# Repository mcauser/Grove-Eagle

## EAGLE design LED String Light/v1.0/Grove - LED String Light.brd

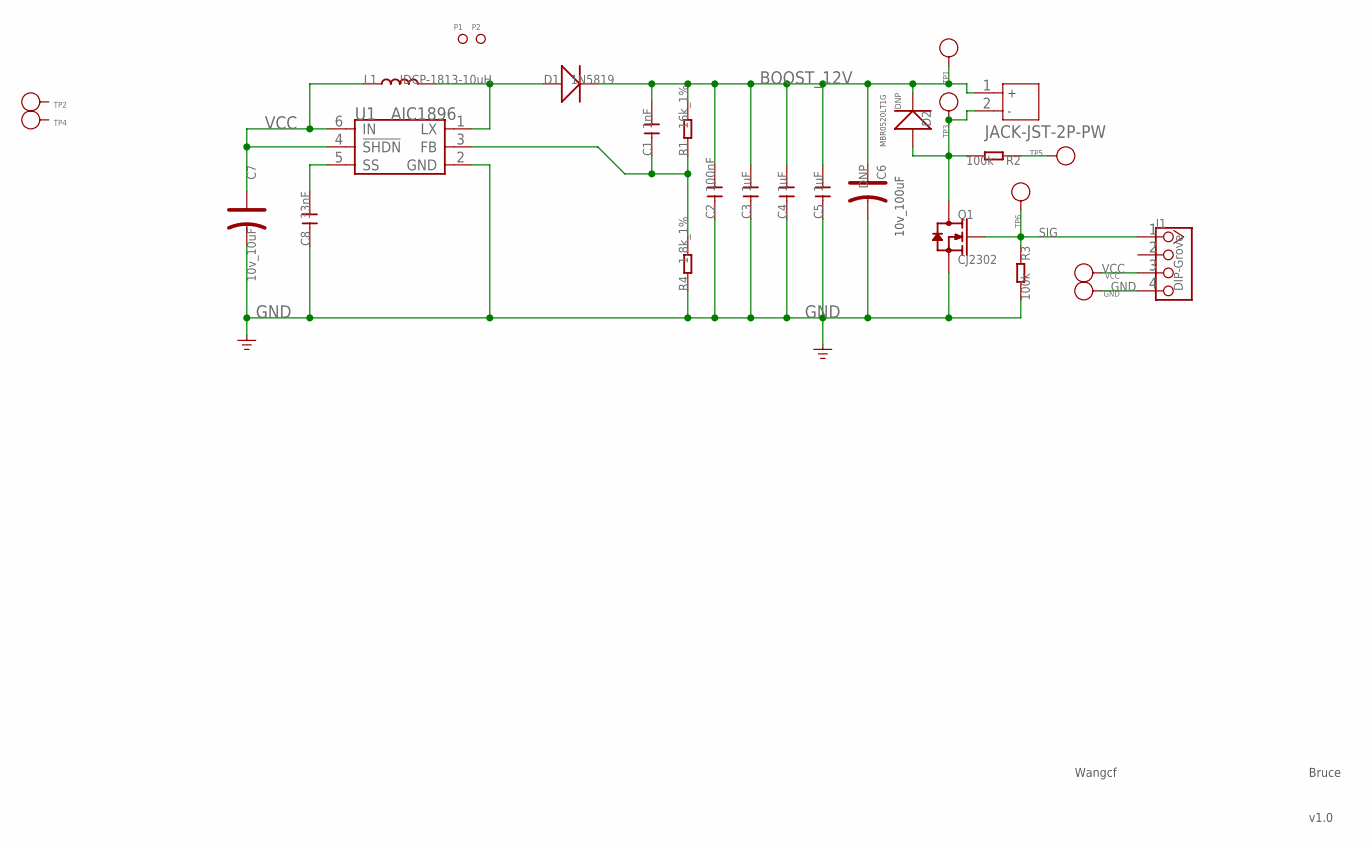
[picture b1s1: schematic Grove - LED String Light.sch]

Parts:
C1: 1nF; C0603
C2: 100nF; C0603
C3, C4, C5: 1uF; C0603
C6: DNP; AVX_C
C7: 10v_10uF; AVX-A
C8: 33nF; C0603
D1: 1N5819; D2010
D2: DNP; SOD123
GND: PAD-TEST-POINT'4545'; TP_4545
J1: DIP-Grove; 4P-2.0
J3: JACK-JST-2P-PW; JST-2.0
L1: IDCP-1813-10uH; 1813@1
P1, P2: PAD-MARK; ROUND-MARK-1.0
Q1: CJ2302; SOT23
R1: 16k_1%; R0603
R2, R3: 100k; R0603
R4: 1.8k_1%; R0603
TP1, TP2, TP3, TP4, TP5, TP6: PAD-TEST-POINT'4545'; TP_4545
U1: AIC1896; SOT23-6
VCC: PAD-TEST-POINT'4545'; TP_4545

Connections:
BOOST_12V: C1.2, C2.2, C3.2, C4.2, C5.2, C6.+, D1.-, D2.-, J3.1, R1.2, TP1.T
GND: C2.1, C3.1, C4.1, C5.1, C6.-, C7.-, C8.1, GND.T, J1.4, Q1.2 (S), R3.2, R4.1, U1.2 (GND)
unnamed: D2.+, J3.2, Q1.3 (D), R2.2, TP3.T
unnamed: R2.1, TP5.T
unnamed: C8.2, U1.5 (SS)
unnamed: D1.+, L1.2, U1.1 (LX)
unnamed: C1.1, R1.1, R4.2, U1.3 (FB)
SIG: J1.1, Q1.1 (G), R3.1, TP6.T
VCC: C7.+, J1.3, L1.1, U1.4 (!SHDN), U1.6 (IN), VCC.T

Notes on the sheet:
MBR0520LT1G
10v_100uF
Wangcf
Bruce
v1.0

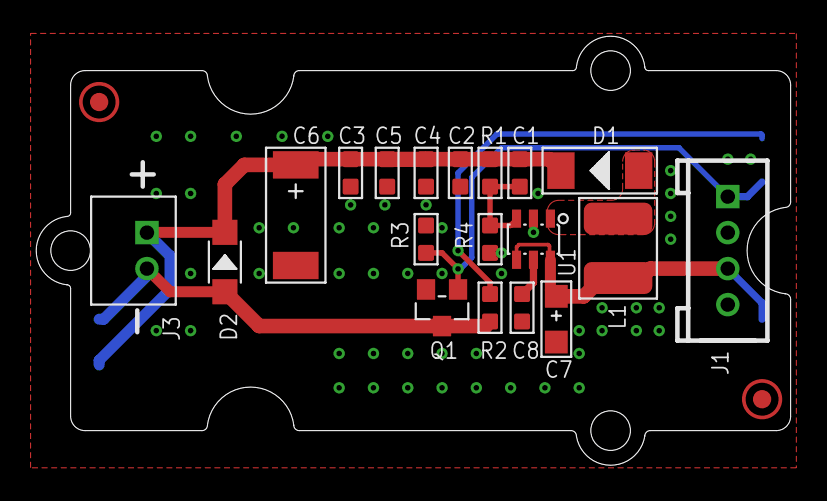
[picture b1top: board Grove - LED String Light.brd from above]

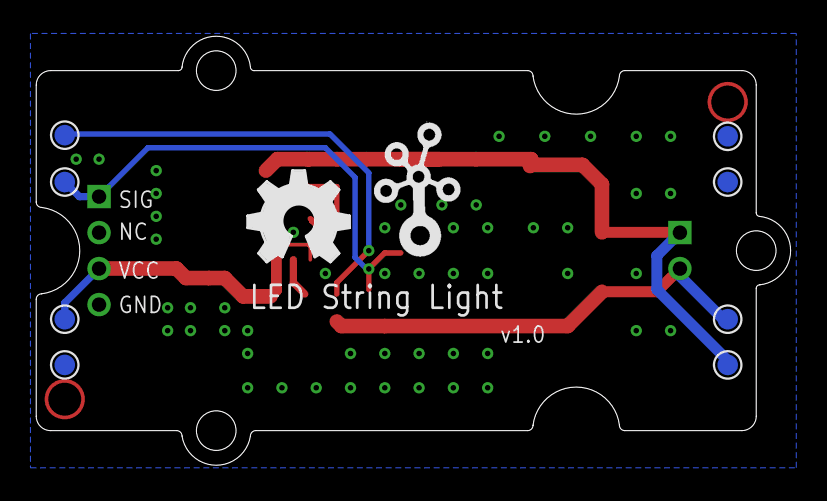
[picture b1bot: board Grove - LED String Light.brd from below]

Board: 4 copper layers, 41.9 x 23.8 mm, 32 parts (10 on the bottom side), 9 nets.

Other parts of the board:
U$4: OSHW_FILLX200_NOTEXT
U$5: GROVE-2CONNECTOR
U$6: TWIGLOGO

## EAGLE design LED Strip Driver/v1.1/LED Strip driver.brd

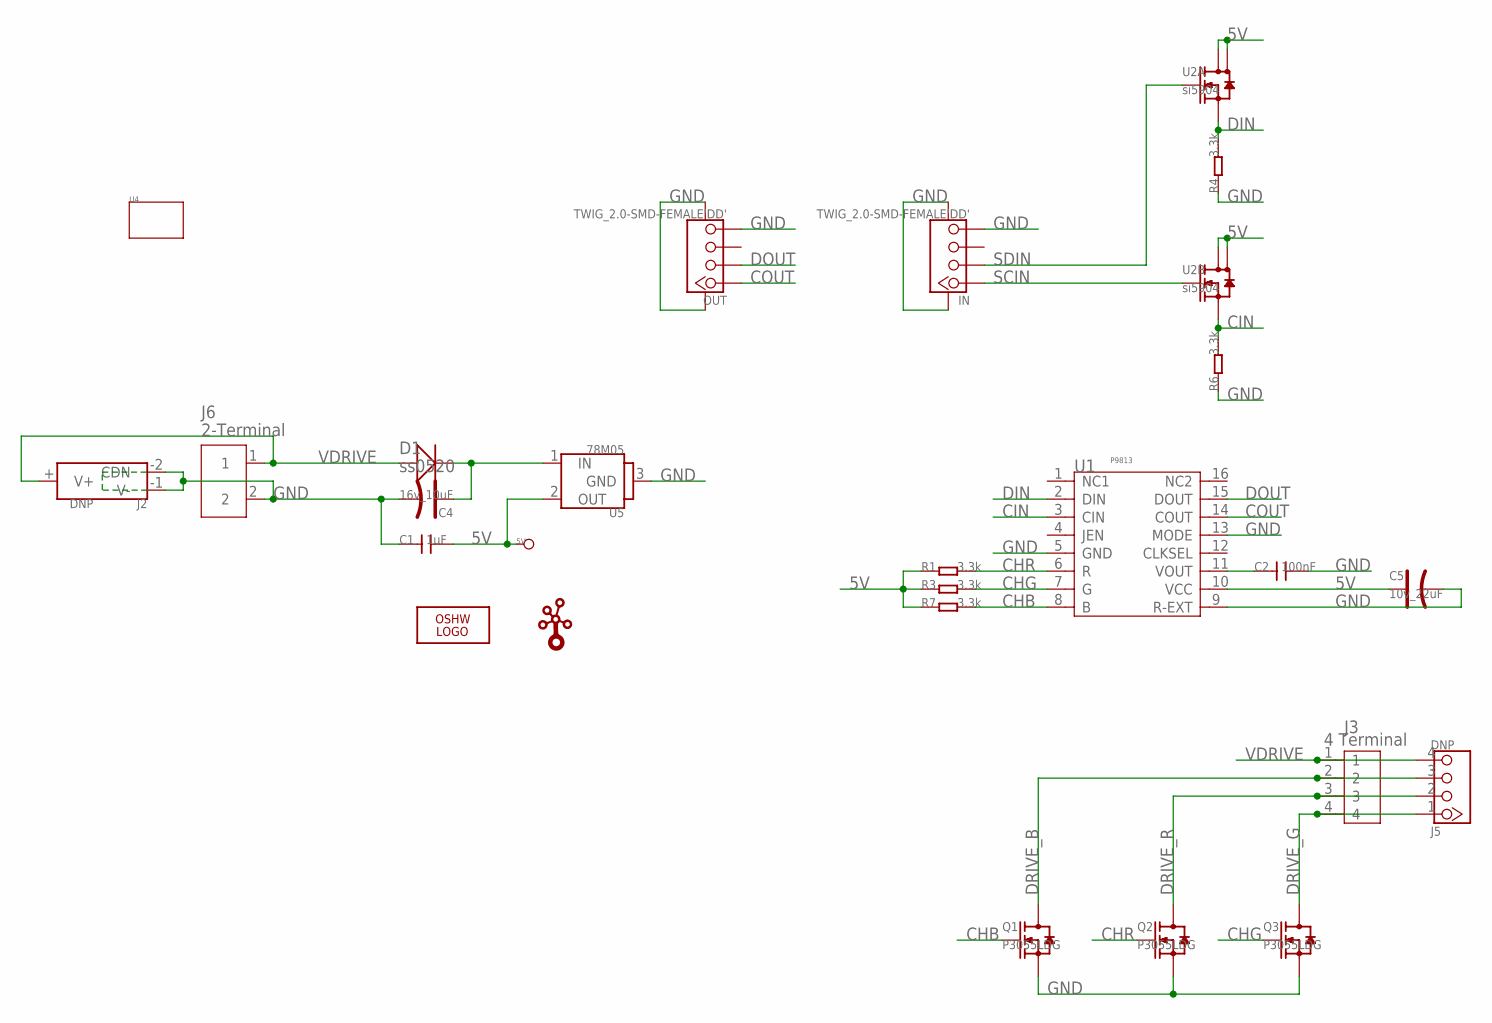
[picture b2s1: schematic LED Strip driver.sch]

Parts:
5V: DNP; TP_3535
C1: 1uF; 0805
C2: 100nF; 0402
C4: 16v_10uF; AVX-A
C5: 10v_22uF; AVX-A
D1: ss0520; SOD123
IN: TWIG_2.0-SMD-FEMALE'DD'; 2.0_1X4DD
J2: DNP; PW-3P-2.5
J3: 4 Terminal; 4P-2.54-15.6X12.2X13.2
J5: DNP; 4P-2.54-90
J6: 2-Terminal; 2P-2.54-12.1X8.5X13.4
LOGO1: LOGO-OSHW-FILLX0200-NT; OSHW_FILLX200_NOTEXT
OUT: TWIG_2.0-SMD-FEMALE'DD'; 2.0_1X4DD
Q1, Q2, Q3: P3055LDG; TO252
R1, R3, R4, R6, R7: 3.3k; 0402
U1: P9813; SSOP16
U2: si5904; 1206-8
U4: TWIG3U-W/O-DRILL; 3U-DIM-W/O-DRILL
U5: 78M05; TO252
U$1: LOGO-TWIG; TWIGLOGO

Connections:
5V: 5V.T, C1.2, C5.+, R1.1, R3.1, R7.1, U1.10 (VCC), U2.5 (D), U2.6 (D), U2.7 (D), U2.8 (D), U5.2 (OUT)
CHB: Q1.1 (G), R7.2, U1.8 (B)
CHG: Q3.1 (G), R3.2, U1.7 (G)
CHR: Q2.1 (G), R1.2, U1.6 (R)
CIN: R6.2, U1.3 (CIN), U2.3 (S)
COUT: OUT.1, U1.14 (COUT)
DIN: R4.2, U1.2 (DIN), U2.1 (S)
DOUT: OUT.2, U1.15 (DOUT)
DRIVE_B: J3.2, J5.3, Q1.2 (D)
DRIVE_G: J3.4, J5.1, Q3.2 (D)
DRIVE_R: J3.3, J5.2, Q2.2 (D)
GND: C1.1, C2.2, C4.-, C5.-, IN.4, IN.SS1, IN.SS2, J2.-1 (V-), J2.-2 (CDN), J6.2, OUT.4, OUT.SS1, OUT.SS2, Q1.3 (S), Q2.3 (S), Q3.3 (S), R4.1, R6.1, U1.5 (GND), U1.9 (R-EXT), U1.13 (MODE), U5.3 (GND)
unnamed: C2.1, U1.11 (VOUT)
unnamed: C4.+, D1.-, U5.1 (IN)
SCIN: IN.1, U2.4 (G)
SDIN: IN.2, U2.2 (G)
VDRIVE: D1.+, J2.+ (V+), J3.1, J5.4, J6.1

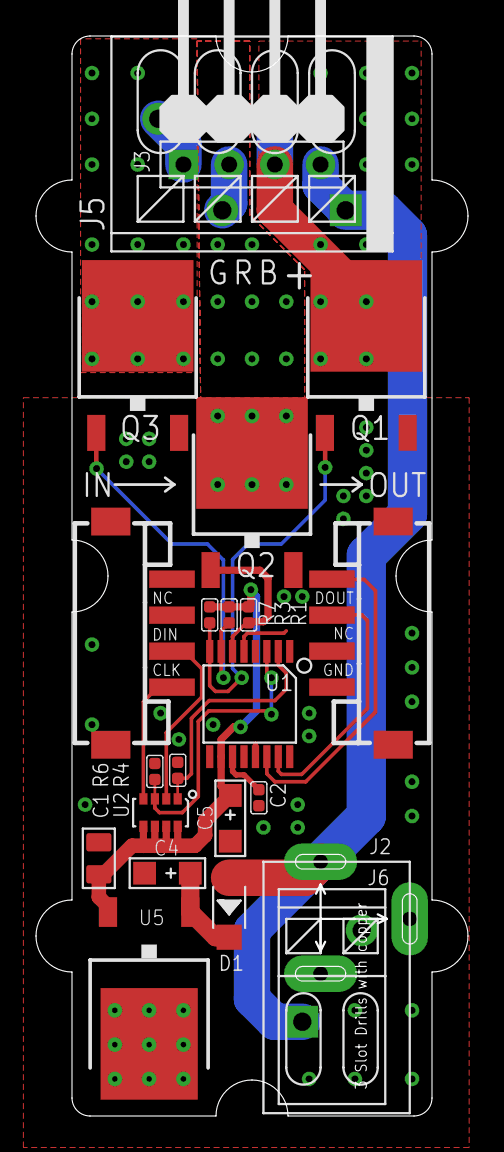
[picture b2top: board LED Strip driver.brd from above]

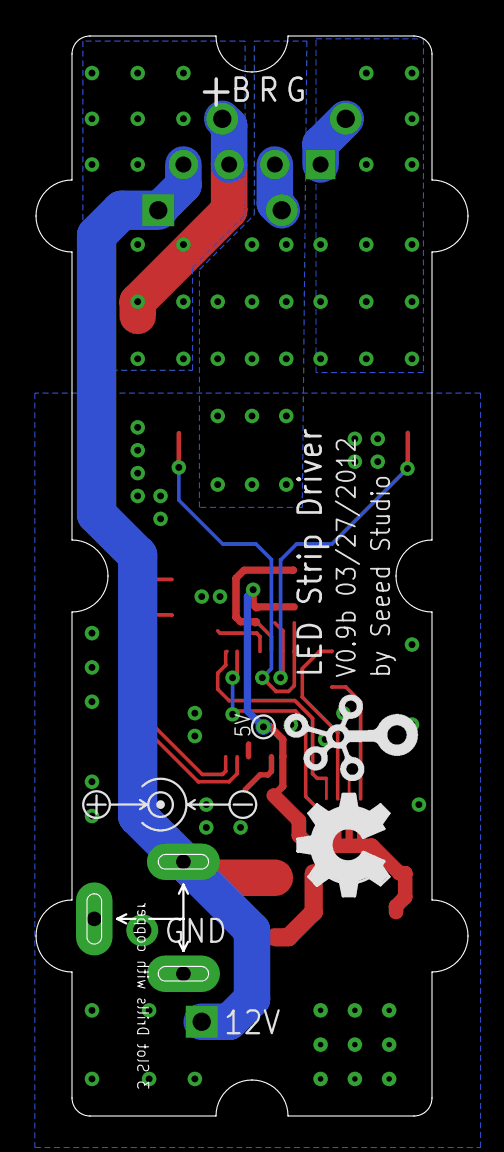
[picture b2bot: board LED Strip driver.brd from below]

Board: 2 copper layers, 24.0 x 60.0 mm, 26 parts (3 on the bottom side), 17 nets.

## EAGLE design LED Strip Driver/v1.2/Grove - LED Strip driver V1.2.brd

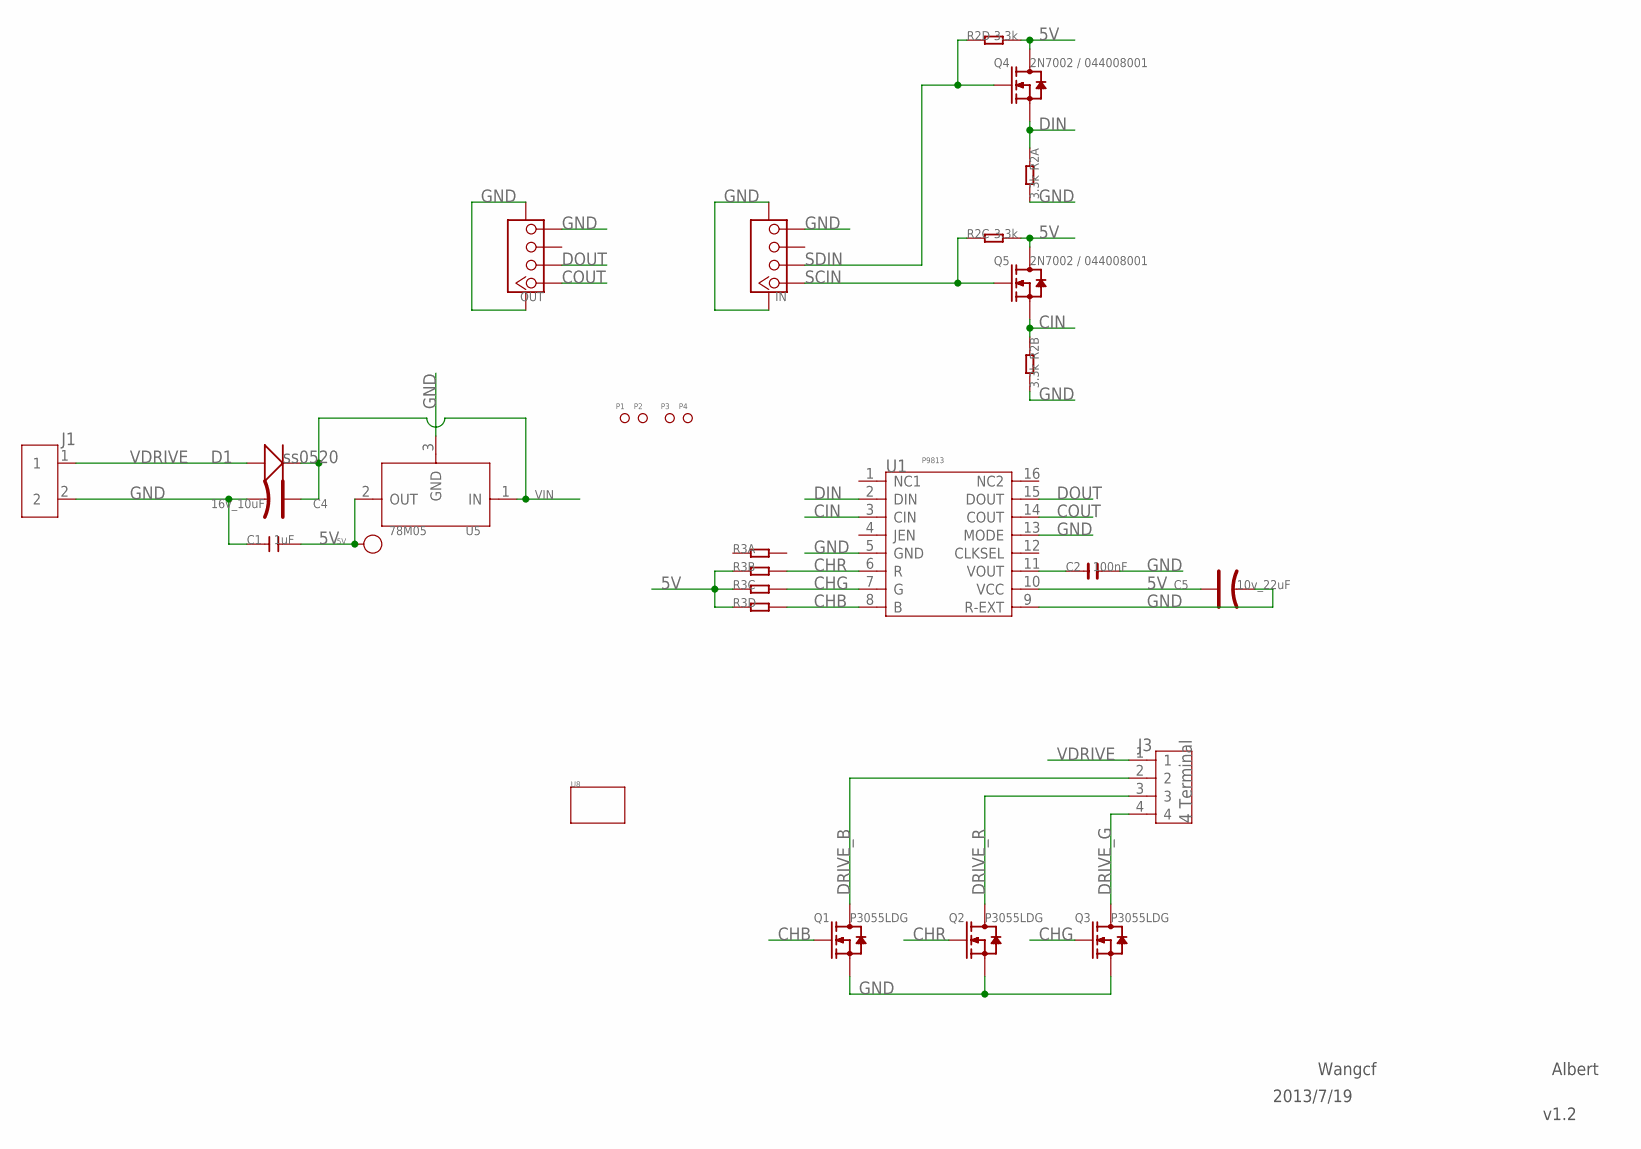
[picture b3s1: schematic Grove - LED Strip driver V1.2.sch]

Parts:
5V: DNP; TP_3535
C1: 1uF; C0805
C2: 100nF; C0603
C4: 16v_10uF; AVX-A
C5: 10v_22uF; AVX-A
D1: ss0520; SOD123
IN: TWIG-4P-2.0-SMD-FEMALE-REINFORCE'DD'; 4P-SMD-2.0
J1: SCREW-TERMINAL-2P'3.5'; 2P-3.5
J3: 4 Terminal; 4P-3.5
OUT: TWIG-4P-2.0-SMD-FEMALE-REINFORCE'DD'; 4P-SMD-2.0
P1, P2, P3, P4: PAD-MARK; ROUND-MARK-1.0
Q1, Q2, Q3: P3055LDG; TO252
Q4, Q5: 2N7002 / 044008001; SOT23
R2: 3.3k; R1206-8
R3: R-4R-1206; 1206-8-3.3X2.4
U1: P9813; SSOP16
U5: 78M05; TO252
U8: TWIG'3U'; 3U-DIM-W/-DRILL

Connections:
5V: 5V.T, C1.2, C5.+, Q4.3 (D), Q5.3 (D), R2.5 (2), R2.6 (2), R3.2 (1), R3.3 (1), R3.4 (1), U1.10 (VCC), U5.2 (OUT)
CHB: Q1.1 (G), R3.5 (2), U1.8 (B)
CHG: Q3.1 (G), R3.6 (2), U1.7 (G)
CHR: Q2.1 (G), R3.7 (2), U1.6 (R)
CIN: Q5.2 (S), R2.2 (1), U1.3 (CIN)
COUT: OUT.1, U1.14 (COUT)
DIN: Q4.2 (S), R2.1, U1.2 (DIN)
DOUT: OUT.2, U1.15 (DOUT)
DRIVE_B: J3.2, Q1.2 (D)
DRIVE_G: J3.4, Q3.2 (D)
DRIVE_R: J3.3, Q2.2 (D)
GND: C1.1, C2.2, C4.-, C5.-, IN.4, IN.SS1, IN.SS2, J1.2, OUT.4, OUT.SS1, OUT.SS2, Q1.3 (S), Q2.3 (S), Q3.3 (S), R2.7 (2), R2.8 (2), U1.5 (GND), U1.9 (R-EXT), U1.13 (MODE), U5.3 (GND)
unnamed: C2.1, U1.11 (VOUT)
SCIN: IN.1, Q5.1 (G), R2.3 (1)
SDIN: IN.2, Q4.1 (G), R2.4 (1)
VDRIVE: D1.+, J1.1, J3.1
VIN: C4.+, D1.-, U5.1 (IN)

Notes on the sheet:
Wangcf
v1.2
Albert
2013/7/19

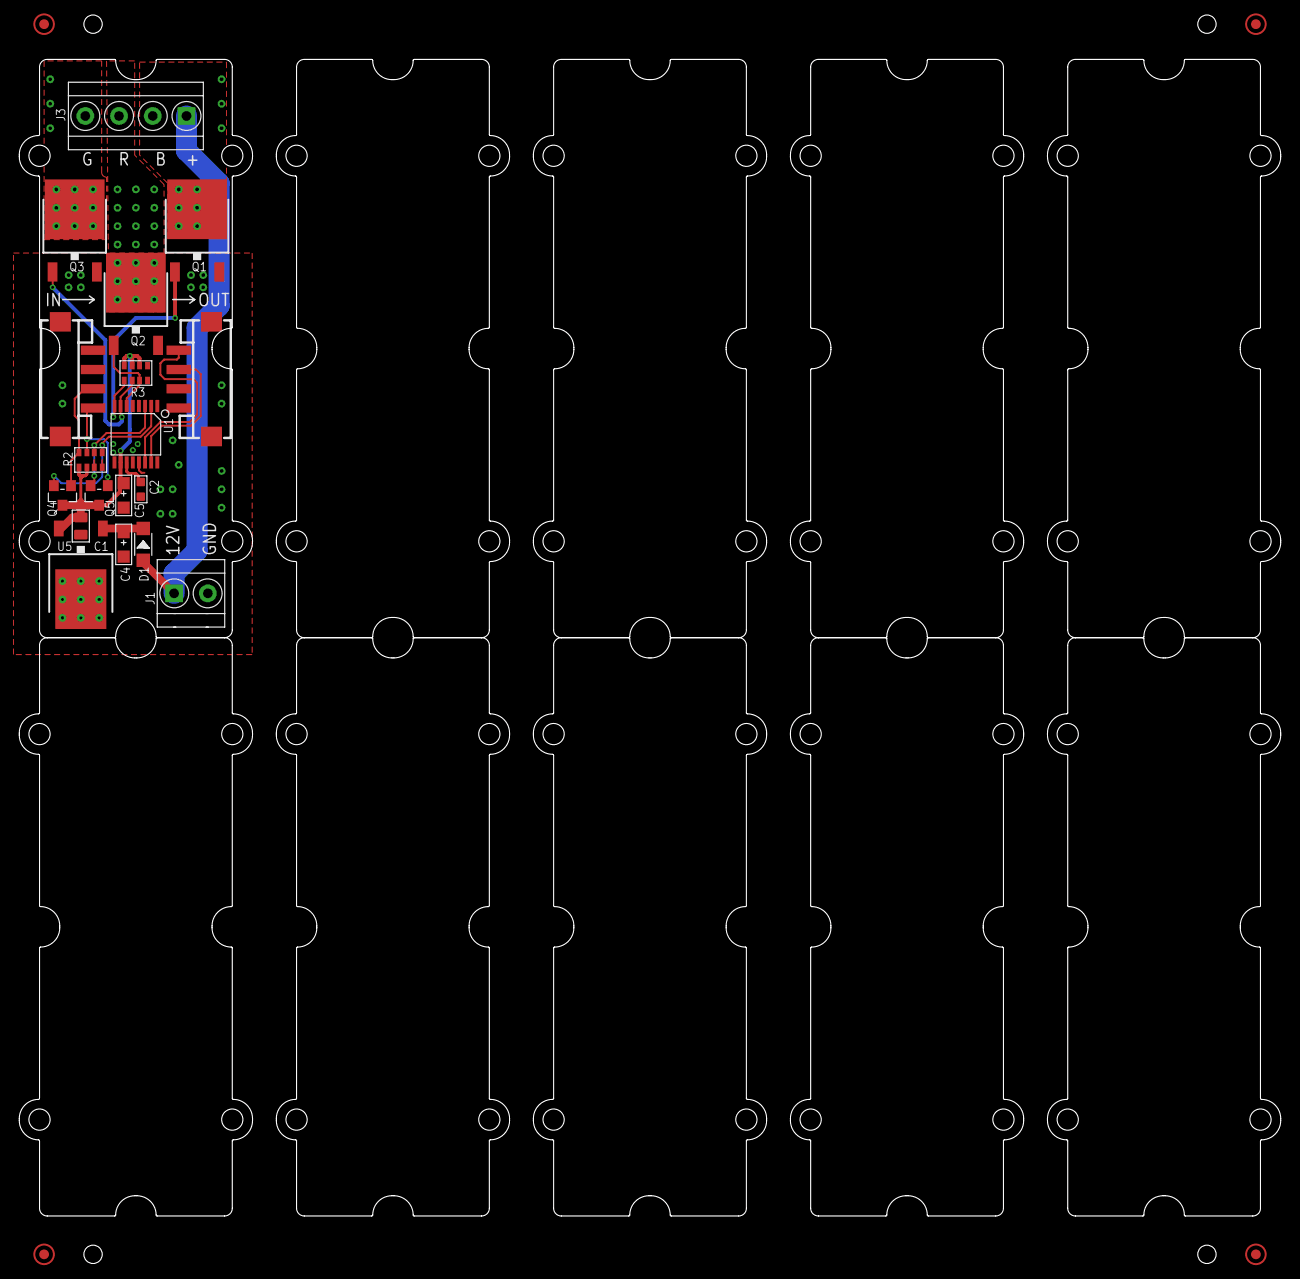
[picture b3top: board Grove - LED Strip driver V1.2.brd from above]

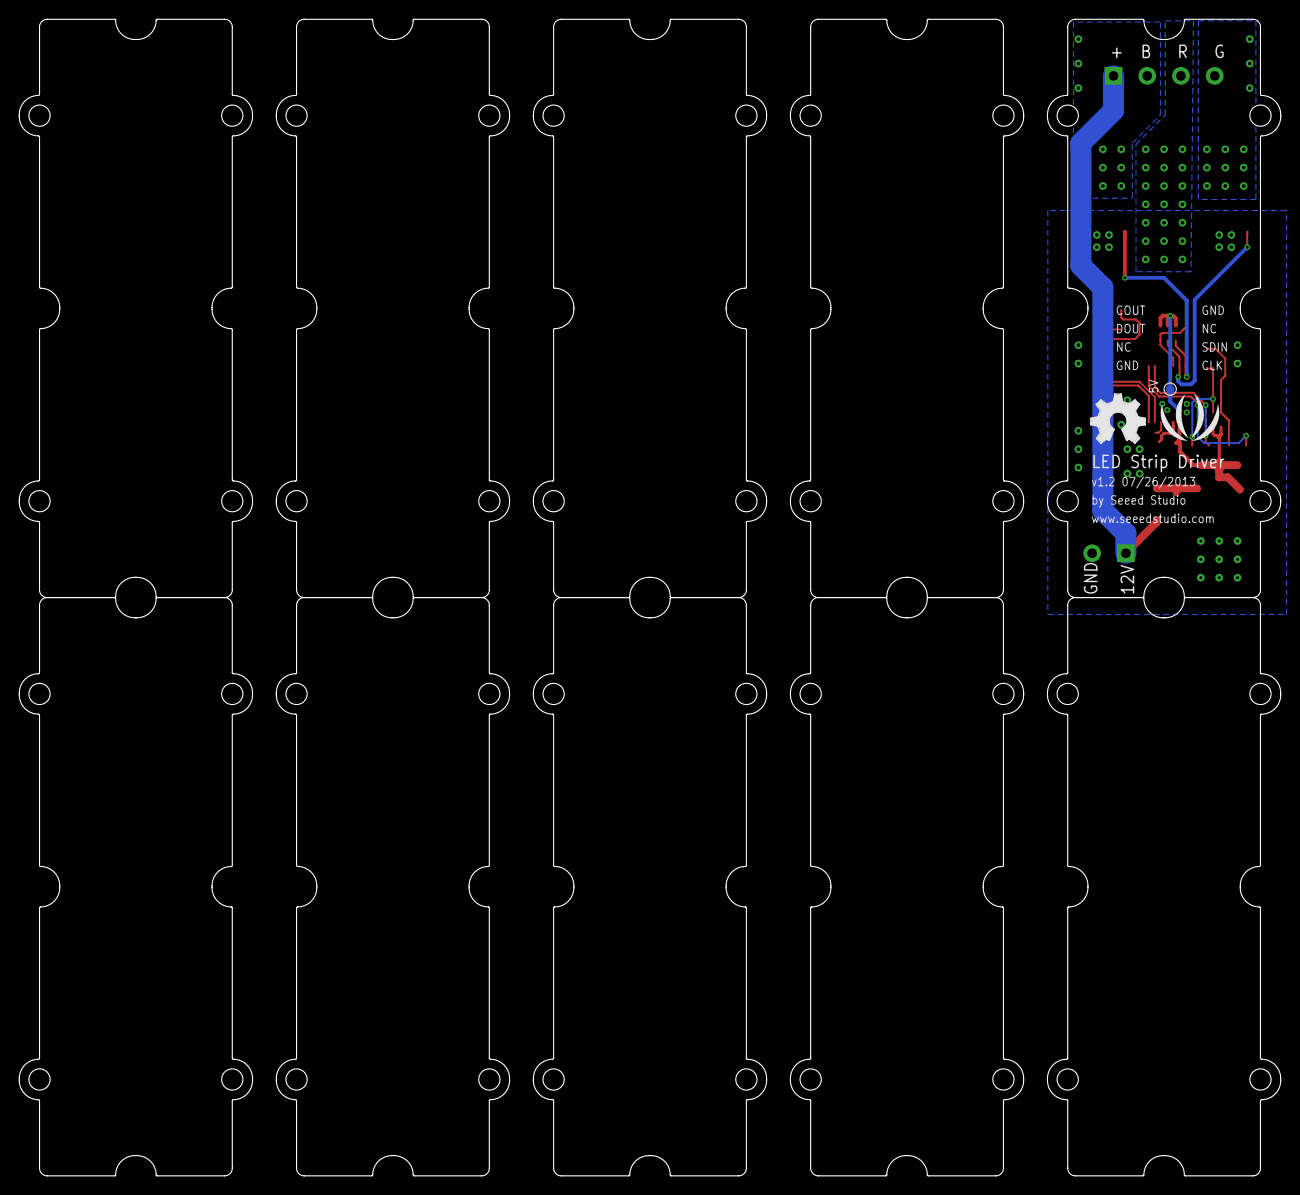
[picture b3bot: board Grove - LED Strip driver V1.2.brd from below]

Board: 2 copper layers, 130.9 x 120.0 mm, 35 parts (3 on the bottom side), 17 nets.

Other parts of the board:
U2, U3, U4, U6, U7, U9, U10, U11, U12: 3U-DIM-W/-DRILL
U$1: LOGO_SILK
U$2: OSHW_FILLX200_NOTEXT

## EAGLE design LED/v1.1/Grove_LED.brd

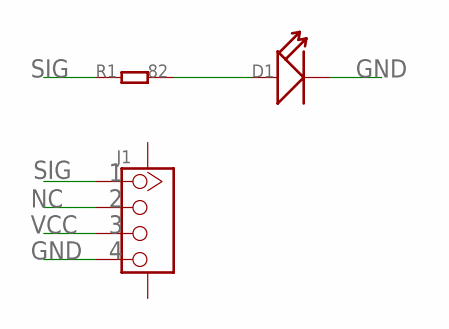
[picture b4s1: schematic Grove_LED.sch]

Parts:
D1: LED-3MM; LED-2P-2.54-3MM
J1: TWIG-4P-2.0-SMD-FEMALE-REINFORCE'90D'; 4P-SMD-2.0-90D
R1: 82; 1206

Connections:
GND: D1.K (-), J1.4
unnamed: D1.A (+), R1.2
NC: J1.2
SIG: J1.1, R1.1
VCC: J1.3

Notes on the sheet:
SIG
GND
VCC

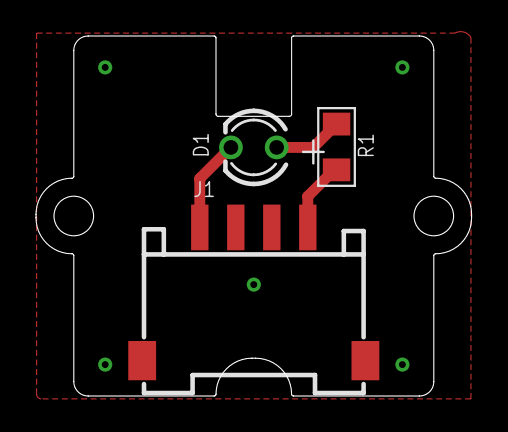
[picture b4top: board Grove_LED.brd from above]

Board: 2 copper layers, 24.2 x 20.0 mm, 5 parts (1 on the bottom side), 3 nets.

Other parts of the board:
U$1: 1U-DIM
U$2: TWIGLOGO

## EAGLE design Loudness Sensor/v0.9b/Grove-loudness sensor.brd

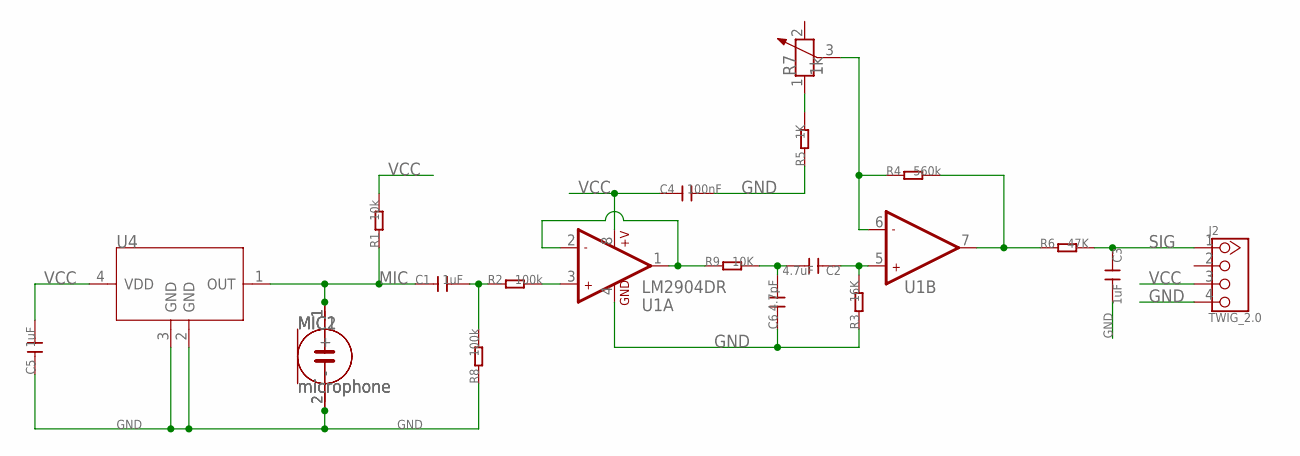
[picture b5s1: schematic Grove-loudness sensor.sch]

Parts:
C1, C3, C5: 1uF; C0603
C2: 4.7uF; C0805
C4: 100nF; C0603
C6: 4.7pF; C0603
J2: TWIG_2.0; 2.0_1X4
MIC1, MIC2: microphone; 2P-D8.9MM
R1: 10k; R0603
R2, R8: 100k; R0603
R3: 16K; R0603
R4: 560k; R0603
R5: 1K; R0603
R6: 47K; R0603
R7: 1k; 3P-SQUA-7X6.8
R9: 10K; R0603
U1: LM2904DR; SO08
U4: SENSOR-MULPS4CX; 4P-SMD-2.95X3.76X1.1H

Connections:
GND: C3.2, C4.2, C5.1, C6.1, J2.4, MIC1.2 (-), MIC2.2 (-), R3.1, R5.1, R8.1, U1.4 (GND), U4.2 (GND), U4.3 (GND)
MIC: C1.1, MIC1.1 (+), MIC2.1 (+), R1.1, U4.1 (OUT)
unnamed: R2.2, U1.3 (+IN1)
unnamed: C1.2, R2.1, R8.2
unnamed: R9.1, U1.1 (OUT1), U1.2 (-IN1)
unnamed: C2.1, R3.2, U1.5 (+IN2)
unnamed: R4.1, R7.3, U1.6 (-IN2)
unnamed: R4.2, R6.1, U1.7 (OUT2)
unnamed: R5.2, R7.1
unnamed: C2.2, C6.2, R9.2
SIG: C3.1, J2.1, R6.2
VCC: C4.1, C5.2, J2.3, R1.2, U1.8 (+V), U4.4 (VDD)

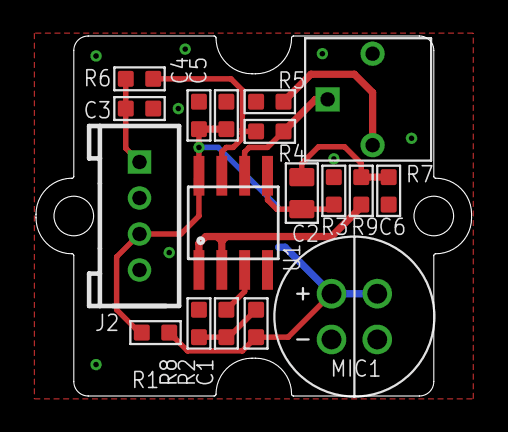
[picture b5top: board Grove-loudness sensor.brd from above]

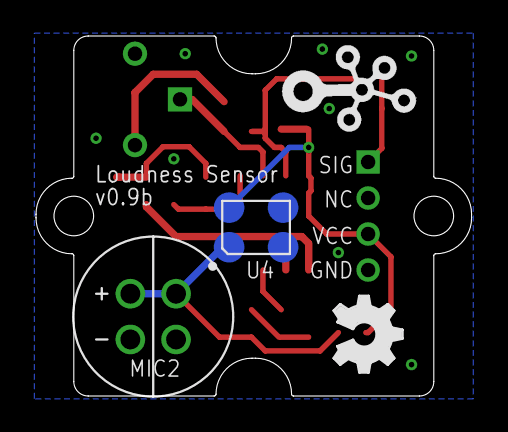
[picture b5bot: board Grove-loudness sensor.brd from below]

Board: 2 copper layers, 24.2 x 20.0 mm, 23 parts (4 on the bottom side), 12 nets.

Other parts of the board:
U$1: OSHW_FILLX150_NOTEXT
U$2: 1U-DIM-W/-DRILL
U$3: TWIGLOGO
